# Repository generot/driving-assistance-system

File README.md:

# Driving Assistance System
Дипломна работа 2023 г. на Мартин Наков - Система за напътстване на шофьор на базата на стерео компютърно зрение.

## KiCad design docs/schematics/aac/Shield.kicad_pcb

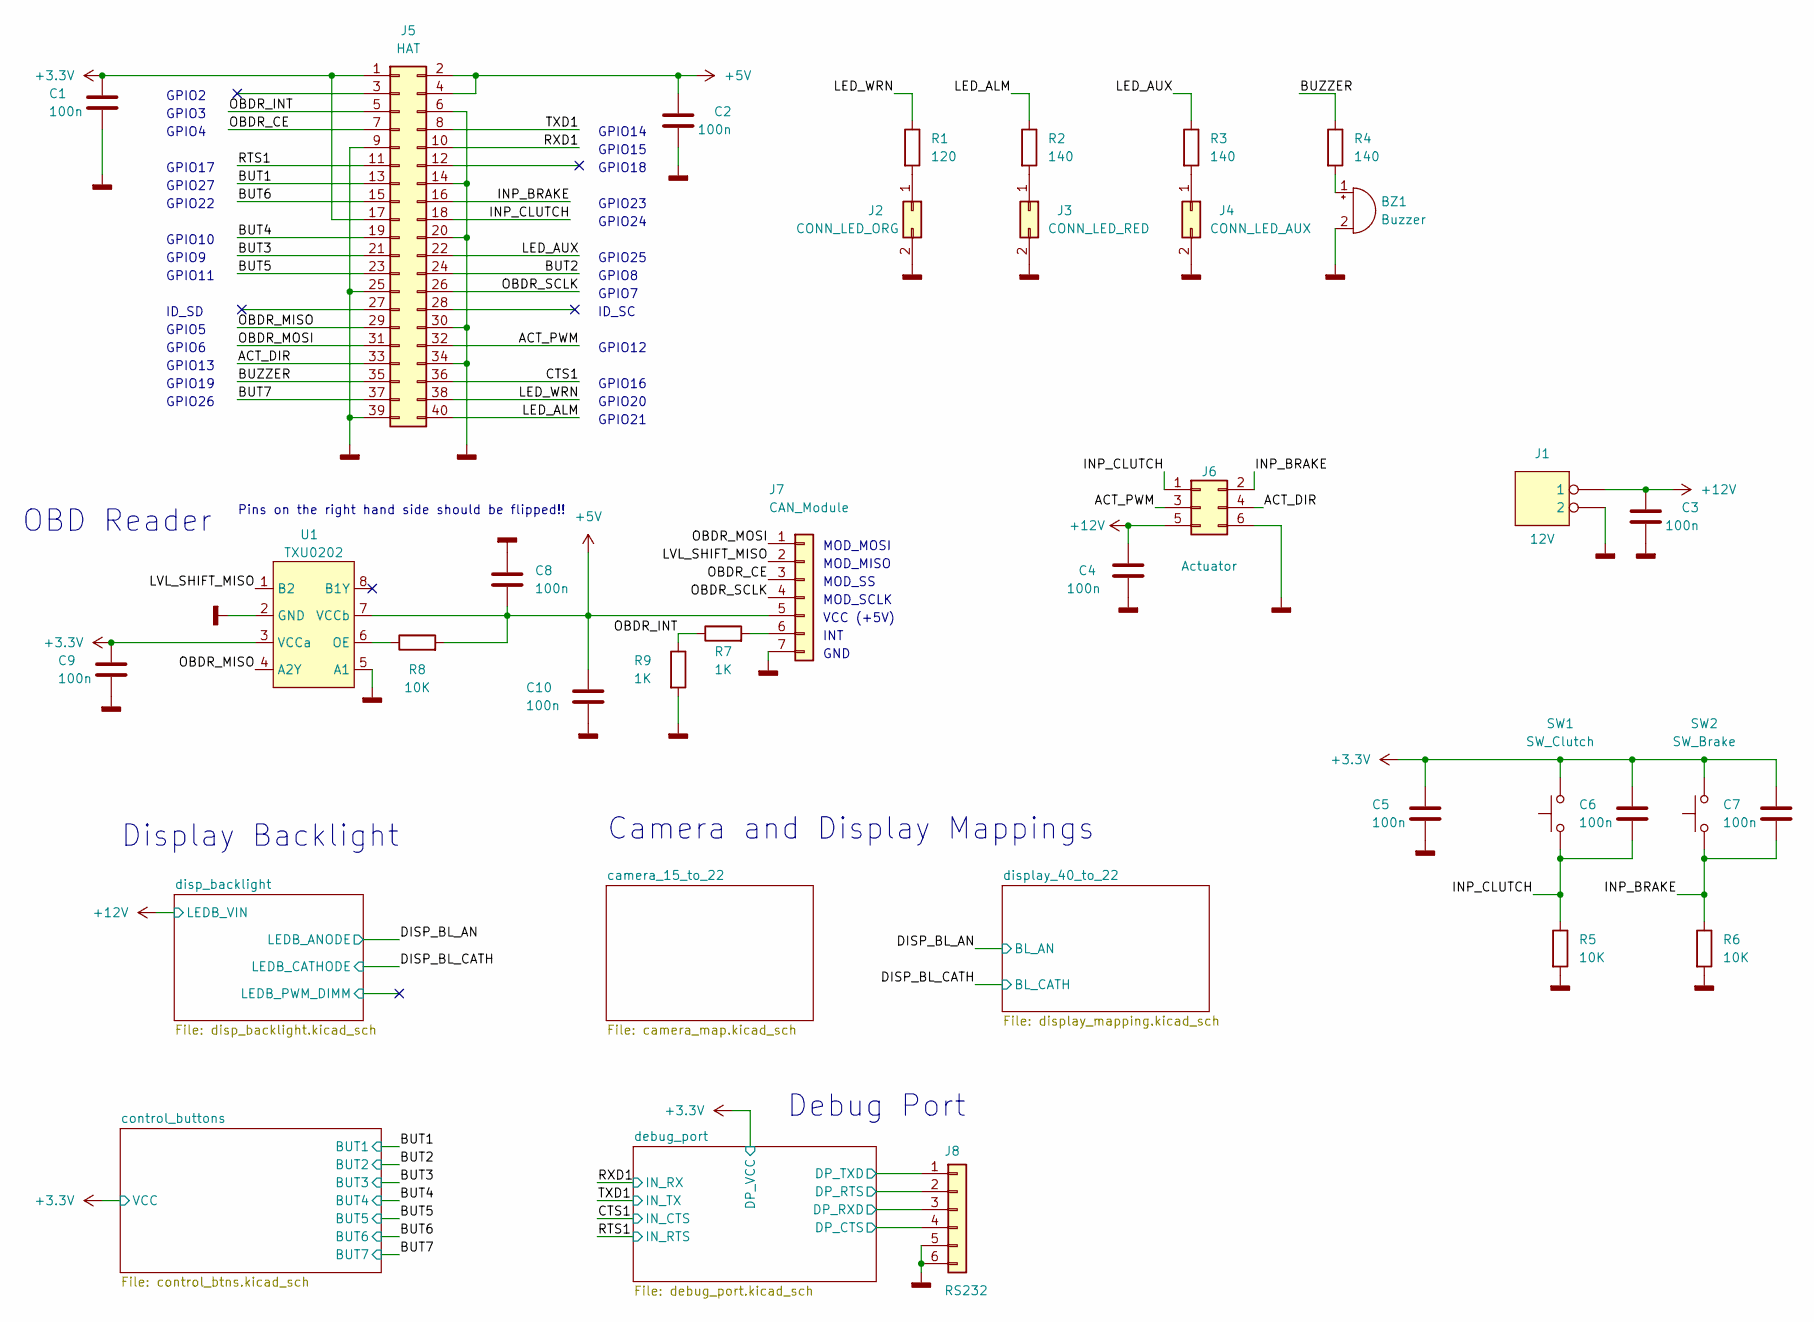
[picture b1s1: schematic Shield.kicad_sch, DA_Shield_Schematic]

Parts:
BZ1: Buzzer; Buzzer_12x9.5RM7.6
C1, C2, C3, C4, C5, C6, C7, C8, C9, C10: 100n; C_0805_2012Metric
J1: 12V; PinHeader_1x02_P2.54mm_Horizontal
J2: CONN_LED_ORG; PinHeader_2x01_P2.54mm_Horizontal
J3: CONN_LED_RED; PinHeader_2x01_P2.54mm_Horizontal
J4: CONN_LED_AUX; PinHeader_2x01_P2.54mm_Horizontal
J5: HAT; PinHeader_2x20_P2.54mm_Vertical
J6: Actuator; PinHeader_2x03_P2.54mm_Vertical
J7: CAN_Module; PinHeader_1x07_P2.54mm_Vertical
J8: RS232; PinHeader_1x06_P2.54mm_Horizontal
R1: 120; R_0805_2012Metric
R2, R3, R4: 140; R_0805_2012Metric
R5, R6, R8: 10K; R_0805_2012Metric
R7, R9: 1K; R_0805_2012Metric
SW1: SW_Clutch; PinHeader_2x01_P2.54mm_Horizontal
SW2: SW_Brake; PinHeader_2x01_P2.54mm_Horizontal
U1: TXU0202; VSSOP-8_2.4x2.1mm_P0.5mm

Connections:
+3.3V: C1.1, C5.1, C6.1, C7.1, C9.1, J5.1, J5.17, SW1.2, SW2.2, U1.3 (VCCa); also elsewhere on the board
+5V: C2.1, C8.1, C10.2, J5.2, J5.4, J7.5, R8.2, U1.7 (VCCb)
+12V: C3.1, C4.1, J1.1, J6.5; also elsewhere on the board
/ACT_DIR: J5.33, J6.4
/ACT_PWM: J5.32, J6.3
/BUT1: J5.13; also elsewhere on the board
/BUT2: J5.24; also elsewhere on the board
/BUT3: J5.21; also elsewhere on the board
/BUT4: J5.19; also elsewhere on the board
/BUT5: J5.23; also elsewhere on the board
/BUT6: J5.15; also elsewhere on the board
/BUT7: J5.37; also elsewhere on the board
/BUZZER: J5.35, R4.1
/CTS1: J5.36; also elsewhere on the board
/INP_BRAKE: C7.2, J5.16, J6.2, R6.1, SW2.1
/INP_CLUTCH: C6.2, J5.18, J6.1, R5.1, SW1.1
/LED_ALM: J5.40, R2.1
/LED_AUX: J5.22, R3.1
/LED_WRN: J5.38, R1.1
/LVL_SHIFT_MISO: J7.2, U1.1 (B2)
/OBDR_CE: J5.7, J7.3
/OBDR_INT: J5.5, R7.1, R9.1
/OBDR_MISO: J5.29, U1.4 (A2Y)
/OBDR_MOSI: J5.31, J7.1
/OBDR_SCLK: J5.26, J7.4
/RTS1: J5.11; also elsewhere on the board
/RXD1: J5.10; also elsewhere on the board
/TXD1: J5.8; also elsewhere on the board
/debug_port/DP_CTS: J8.4; also elsewhere on the board
/debug_port/DP_RTS: J8.2; also elsewhere on the board
/debug_port/DP_RXD: J8.3; also elsewhere on the board
/debug_port/DP_TXD: J8.1; also elsewhere on the board
GNDD: BZ1.2 (+), C1.2, C2.2, C3.2, C4.2, C5.2, C8.2, C9.2, C10.1, J1.2, J2.2, J3.2, J4.2, J5.6, J5.9, J5.14, J5.20, J5.25, J5.30, J5.34, J5.39, J6.6, J7.7, J8.5, J8.6, R5.2, R6.2, R9.2, U1.2 (GND), U1.5 (A1); also elsewhere on the board
unnamed: BZ1.1 (-), R4.2
unnamed: J2.1, R1.2
unnamed: J3.1, R2.2
unnamed: J4.1, R3.2
unnamed: J7.6, R7.2
unnamed: R8.1, U1.6 (OE)

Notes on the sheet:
INT
OBD Reader
GPIO15
GPIO2
GPIO5
GPIO25
GPIO18
GPIO4
GND
GPIO11
MOD_MISO
GPIO8
GPIO10
GPIO16
GPIO7
GPIO23
GPIO22
GPIO17
MOD_SS
MOD_MOSI
GPIO14
GPIO6
GPIO19
GPIO24
Pins on the right hand side should be flipped!!
GPIO9
GPIO3
MOD_SCLK
GPIO20
GPIO21
GPIO12
GPIO26
ID_SC
GPIO27
Display Backlight
GPIO13
ID_SD
Debug Port
VCC (+5V)
Camera and Display Mappings

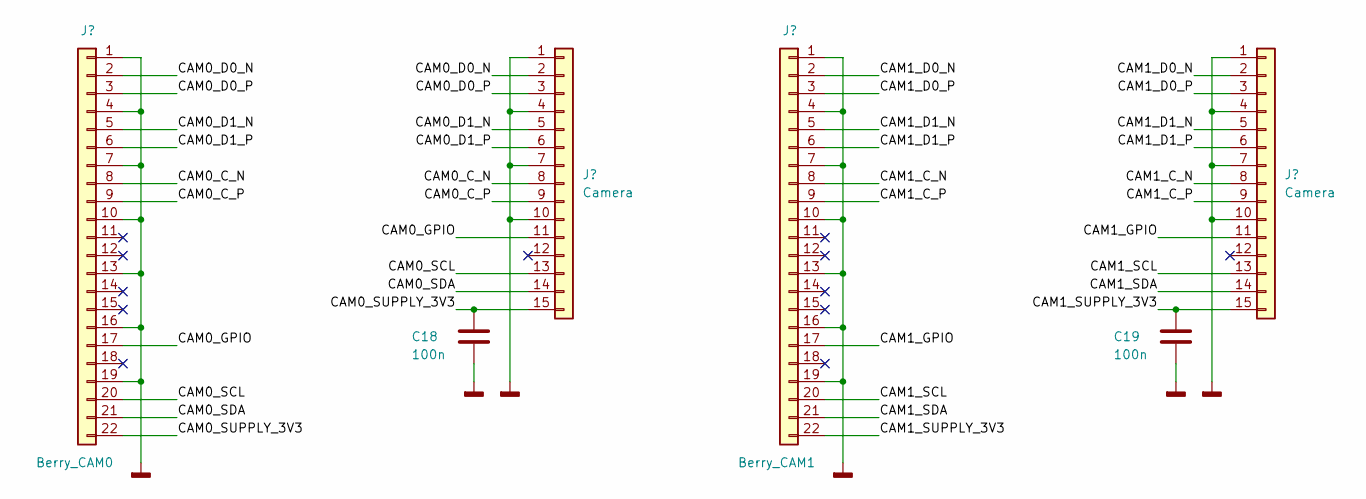
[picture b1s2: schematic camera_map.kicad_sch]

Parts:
C18, C19: 100n; C_0805_2012Metric
J9, J10: Camera; TE_1-84952-5_1x15-1MP_P1.0mm_Horizontal
J11: Berry_CAM0; Hirose_FH12-22S-0.5SH_1x22-1MP_P0.50mm_Horizontal
J12: Berry_CAM1; Hirose_FH12-22S-0.5SH_1x22-1MP_P0.50mm_Horizontal

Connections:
/camera_15_to_22/CAM0_C_N: J9.8, J11.8
/camera_15_to_22/CAM0_C_P: J9.9, J11.9
/camera_15_to_22/CAM0_D0_N: J9.2, J11.2
/camera_15_to_22/CAM0_D0_P: J9.3, J11.3
/camera_15_to_22/CAM0_D1_N: J9.5, J11.5
/camera_15_to_22/CAM0_D1_P: J9.6, J11.6
/camera_15_to_22/CAM0_GPIO: J9.11, J11.17
/camera_15_to_22/CAM0_SCL: J9.13, J11.20
/camera_15_to_22/CAM0_SDA: J9.14, J11.21
/camera_15_to_22/CAM0_SUPPLY_3V3: C18.1, J9.15, J11.22
/camera_15_to_22/CAM1_C_N: J10.8, J12.8
/camera_15_to_22/CAM1_C_P: J10.9, J12.9
/camera_15_to_22/CAM1_D0_N: J10.2, J12.2
/camera_15_to_22/CAM1_D0_P: J10.3, J12.3
/camera_15_to_22/CAM1_D1_N: J10.5, J12.5
/camera_15_to_22/CAM1_D1_P: J10.6, J12.6
/camera_15_to_22/CAM1_GPIO: J10.11, J12.17
/camera_15_to_22/CAM1_SCL: J10.13, J12.20
/camera_15_to_22/CAM1_SDA: J10.14, J12.21
/camera_15_to_22/CAM1_SUPPLY_3V3: C19.1, J10.15, J12.22
GNDD: C18.2, C19.2, J9.1, J9.4, J9.7, J9.10, J9.MP, J10.1, J10.4, J10.7, J10.10, J10.MP, J11.1, J11.4, J11.7, J11.10, J11.13, J11.16, J11.19, J11.MP, J12.1, J12.4, J12.7, J12.10, J12.13, J12.16, J12.19, J12.MP; also elsewhere on the board

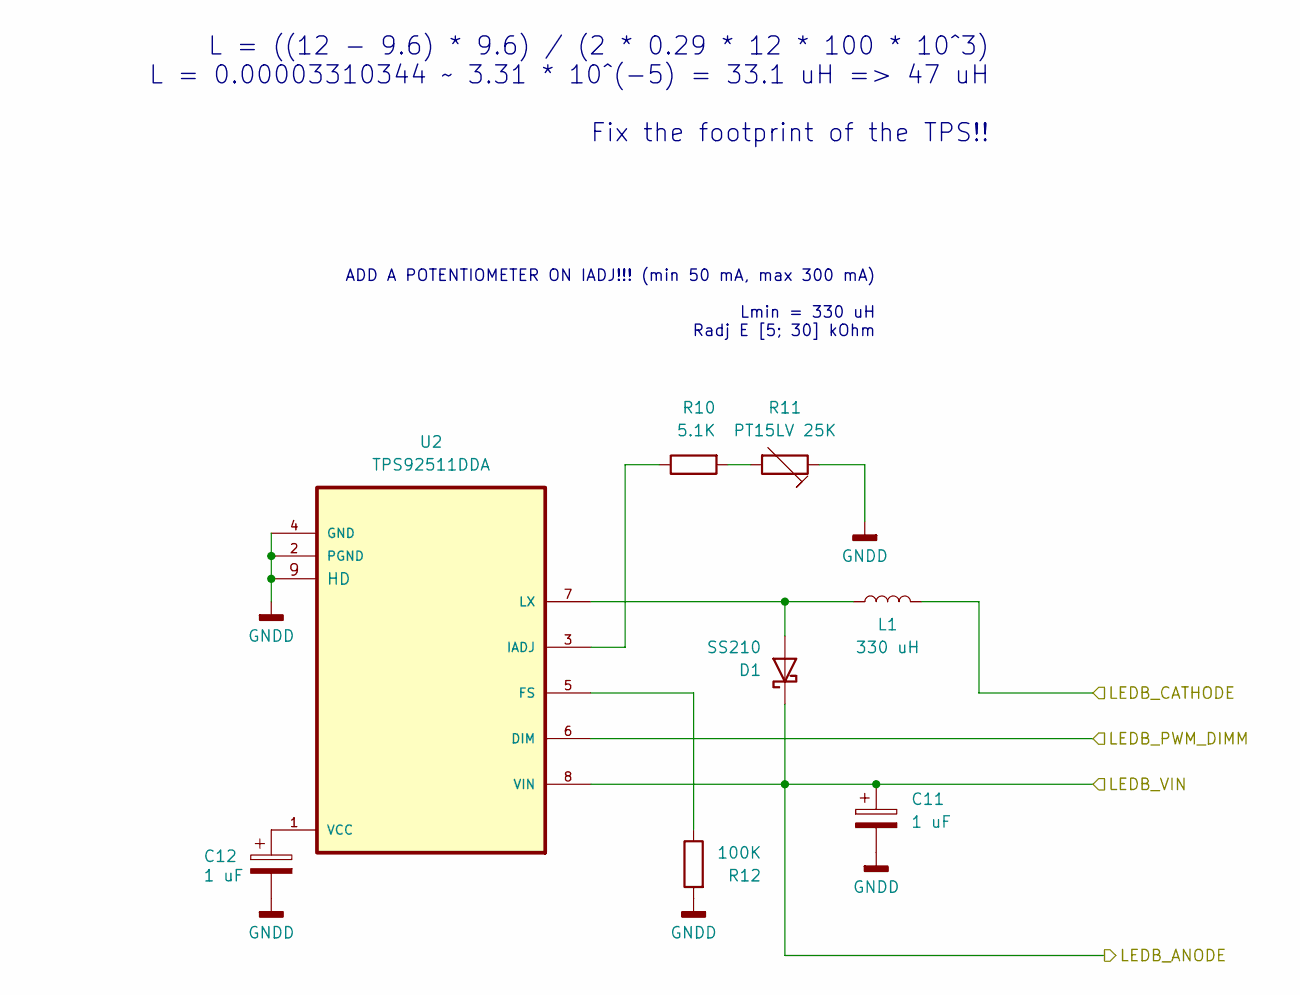
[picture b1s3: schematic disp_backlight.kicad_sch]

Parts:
C11, C12: 1 uF; C_0805_2012Metric
D1: SS210; D_SMB
L1: 330 uH; L_SigTra_SC3316F
R10: 5.1K; R_0805_2012Metric
R11: PT15LV 25K; Potentiometer_ACP_CA14V-15_Vertical
R12: 100K; R_0805_2012Metric
U2: TPS92511DDA; SOIC-8-1EP_3.9x4.9mm_P1.27mm_EP2.29x3mm_ThermalVias

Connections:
+12V: C11.1, D1.1 (K), U2.8 (VIN); also elsewhere on the board
/DISP_BL_CATH: L1.2; also elsewhere on the board
/disp_backlight/LEDB_PWM_DIMM: U2.6 (DIM)
GNDD: C11.2, C12.2, R11.1, R12.2, U2.2 (PGND), U2.4 (GND), U2.9 (HD); also elsewhere on the board
unnamed: D1.2 (A), L1.1, U2.7 (LX)
unnamed: R10.2, R11.2
unnamed: R12.1, U2.5 (FS)
unnamed: R10.1, U2.3 (IADJ)
unnamed: C12.1, U2.1 (VCC)

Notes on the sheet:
ADD A POTENTIOMETER ON IADJ!!! (min 50 mA, max 300 mA) Lmin = 330 uH Radj E [5; 30] kOhm
L = ((12 - 9.6) * 9.6) / (2 * 0.29 * 12 * 100 * 10^3) L = 0.00003310344 ~ 3.31 * 10^(-5) = 33.1 uH => 47 uH Fix the footprint of the TPS!!

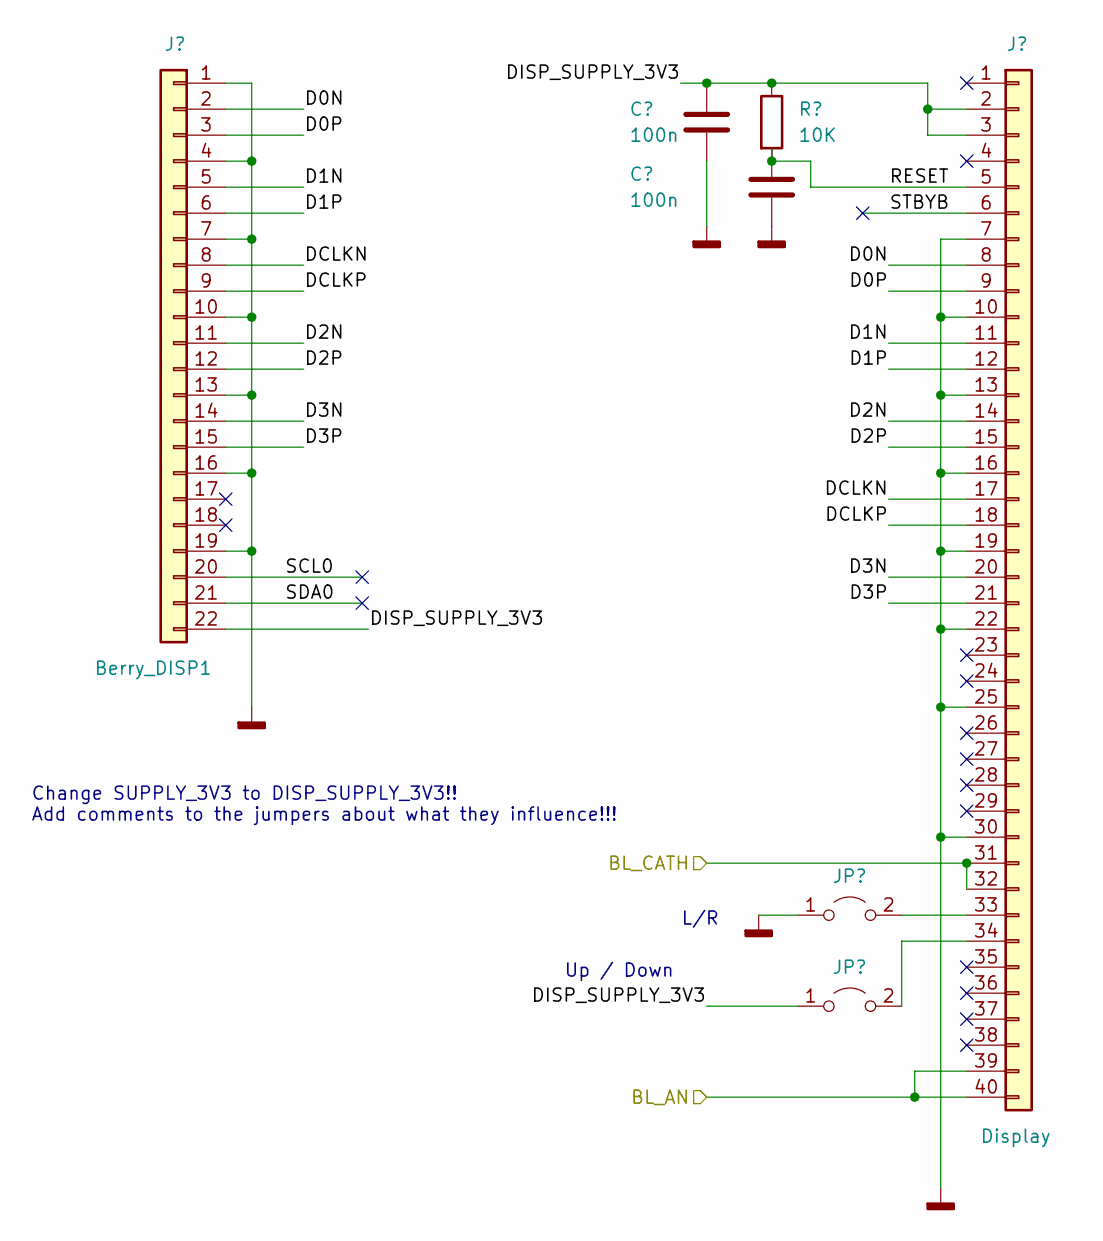
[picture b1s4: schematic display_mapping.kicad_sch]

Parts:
C28, C29: 100n; C_0805_2012Metric
J20: Berry_DISP1; Hirose_FH12-22S-0.5SH_1x22-1MP_P0.50mm_Horizontal
J21: Display; Hirose_FH12-40S-0.5SH_1x40-1MP_P0.50mm_Horizontal
JP1, JP2: Jumper_2_Open; SolderJumper-2_P1.3mm_Open_RoundedPad1.0x1.5mm
R20: 10K; R_0805_2012Metric

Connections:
+12V: J21.39, J21.40; also elsewhere on the board
/DISP_BL_CATH: J21.31, J21.32; also elsewhere on the board
/display_40_to_22/D0N: J20.2, J21.8
/display_40_to_22/D0P: J20.3, J21.9
/display_40_to_22/D1N: J20.5, J21.11
/display_40_to_22/D1P: J20.6, J21.12
/display_40_to_22/D2N: J20.11, J21.14
/display_40_to_22/D2P: J20.12, J21.15
/display_40_to_22/D3N: J20.14, J21.20
/display_40_to_22/D3P: J20.15, J21.21
/display_40_to_22/DCLKN: J20.8, J21.17
/display_40_to_22/DCLKP: J20.9, J21.18
/display_40_to_22/DISP_SUPPLY_3V3: C28.1, J20.22, J21.2, J21.3, JP2.1 (A), R20.1
/display_40_to_22/RESET: C29.1, J21.5, R20.2
/display_40_to_22/SCL0: J20.20
/display_40_to_22/SDA0: J20.21
/display_40_to_22/STBYB: J21.6
GNDD: C28.2, C29.2, J20.1, J20.4, J20.7, J20.10, J20.13, J20.16, J20.19, J20.MP, J21.7, J21.10, J21.13, J21.16, J21.19, J21.22, J21.25, J21.30, J21.MP, JP1.1 (A); also elsewhere on the board
unnamed: J21.33, JP1.2 (B)
unnamed: J21.34, JP2.2 (B)

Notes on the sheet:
L/R
Change SUPPLY_3V3 to DISP_SUPPLY_3V3!! Add comments to the jumpers about what they influence!!!
Up / Down

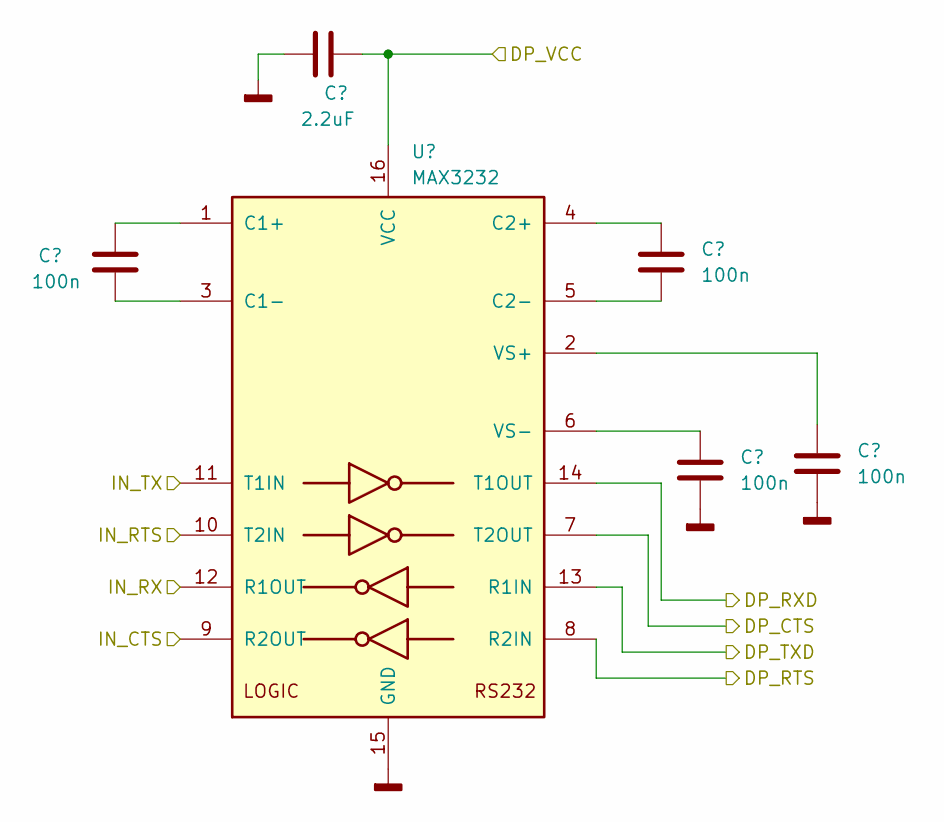
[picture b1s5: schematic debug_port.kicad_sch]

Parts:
C13: 2.2uF; C_0805_2012Metric
C14, C15, C16, C17: 100n; C_0805_2012Metric
U3: MAX3232; SO-16_5.3x10.2mm_P1.27mm

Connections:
+3.3V: C13.2, U3.16 (VCC); also elsewhere on the board
/CTS1: U3.9 (R2OUT); also elsewhere on the board
/RTS1: U3.10 (T2IN); also elsewhere on the board
/RXD1: U3.12 (R1OUT); also elsewhere on the board
/TXD1: U3.11 (T1IN); also elsewhere on the board
/debug_port/DP_CTS: U3.7 (T2OUT); also elsewhere on the board
/debug_port/DP_RTS: U3.8 (R2IN); also elsewhere on the board
/debug_port/DP_RXD: U3.14 (T1OUT); also elsewhere on the board
/debug_port/DP_TXD: U3.13 (R1IN); also elsewhere on the board
GNDD: C13.1, C16.2, C17.2, U3.15 (GND); also elsewhere on the board
unnamed: C14.1, U3.1 (C1+)
unnamed: C14.2, U3.3 (C1-)
unnamed: C15.1, U3.4 (C2+)
unnamed: C15.2, U3.5 (C2-)
unnamed: C16.1, U3.2 (VS+)
unnamed: C17.1, U3.6 (VS-)

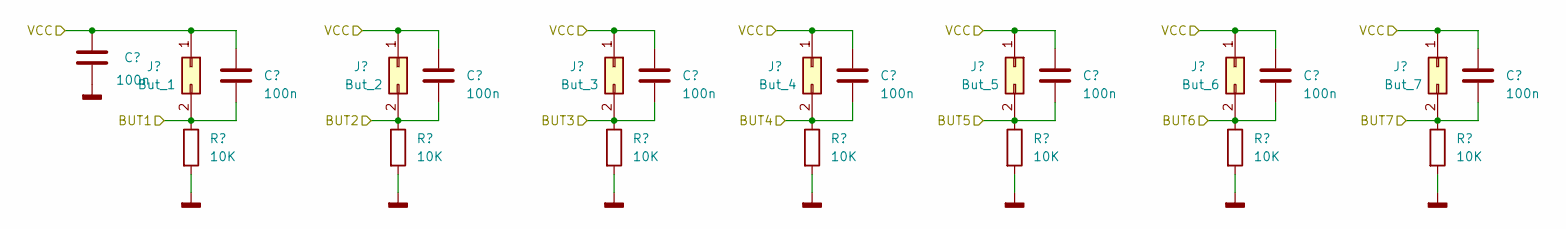
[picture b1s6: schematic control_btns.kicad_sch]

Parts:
C20, C21, C22, C23, C24, C25, C26, C27: 100n; C_0805_2012Metric
J13: But_1; PinHeader_2x01_P2.54mm_Horizontal
J14: But_2; PinHeader_2x01_P2.54mm_Horizontal
J15: But_3; PinHeader_2x01_P2.54mm_Horizontal
J16: But_4; PinHeader_2x01_P2.54mm_Horizontal
J17: But_5; PinHeader_2x01_P2.54mm_Horizontal
J18: But_6; PinHeader_2x01_P2.54mm_Horizontal
J19: But_7; PinHeader_2x01_P2.54mm_Horizontal
R13, R14, R15, R16, R17, R18, R19: 10K; R_0805_2012Metric

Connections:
+3.3V: C20.1, C21.1, C22.1, C23.1, C24.1, C25.1, C26.1, C27.1, J13.1, J14.1, J15.1, J16.1, J17.1, J18.1, J19.1; also elsewhere on the board
/BUT1: C21.2, J13.2, R13.1; also elsewhere on the board
/BUT2: C22.2, J14.2, R14.1; also elsewhere on the board
/BUT3: C23.2, J15.2, R15.1; also elsewhere on the board
/BUT4: C24.2, J16.2, R16.1; also elsewhere on the board
/BUT5: C25.2, J17.2, R17.1; also elsewhere on the board
/BUT6: C26.2, J18.2, R18.1; also elsewhere on the board
/BUT7: C27.2, J19.2, R19.1; also elsewhere on the board
GNDD: C20.2, R13.2, R14.2, R15.2, R16.2, R17.2, R18.2, R19.2; also elsewhere on the board

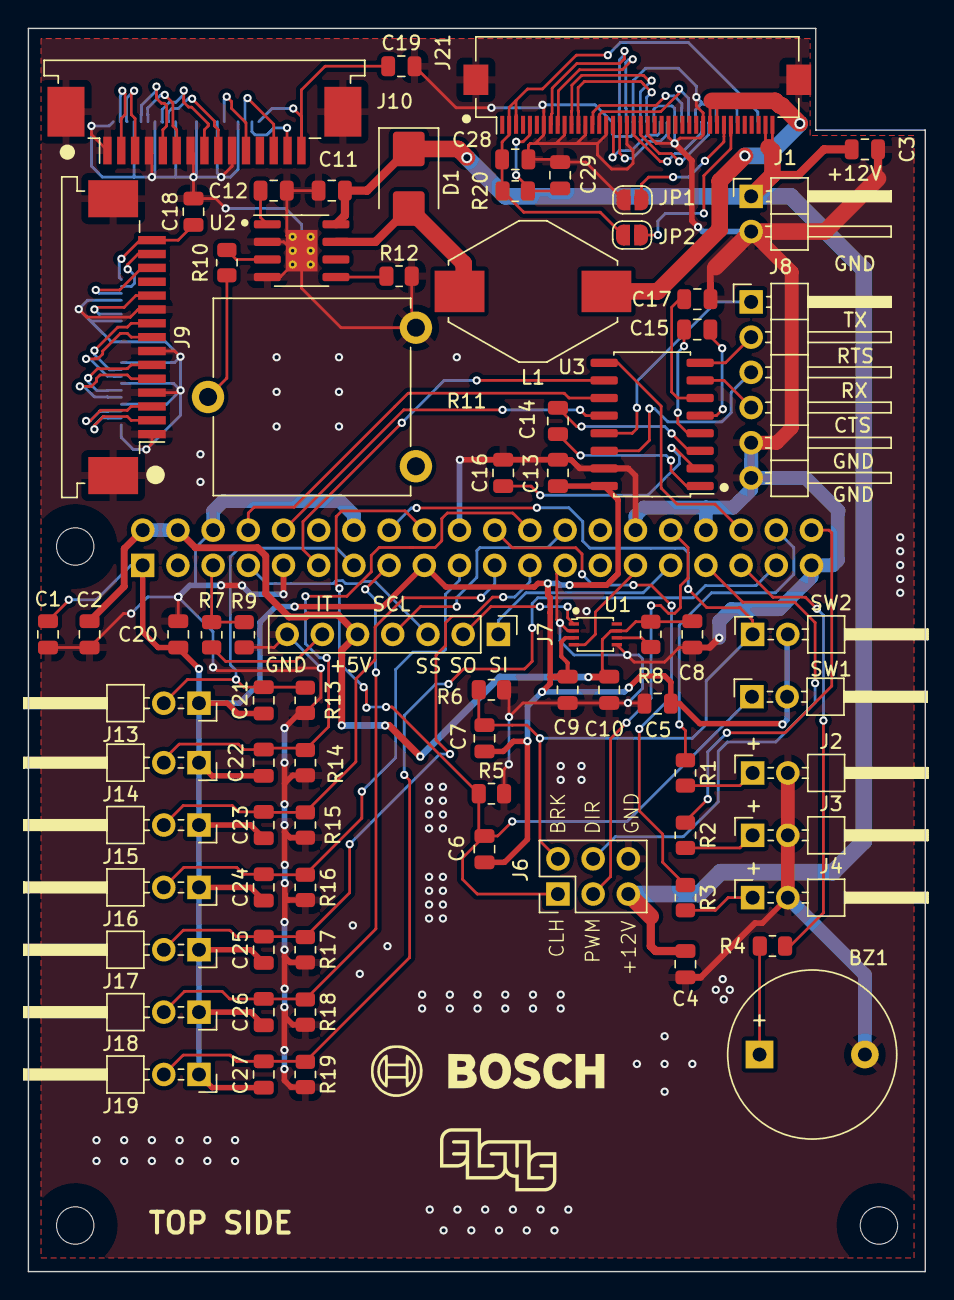
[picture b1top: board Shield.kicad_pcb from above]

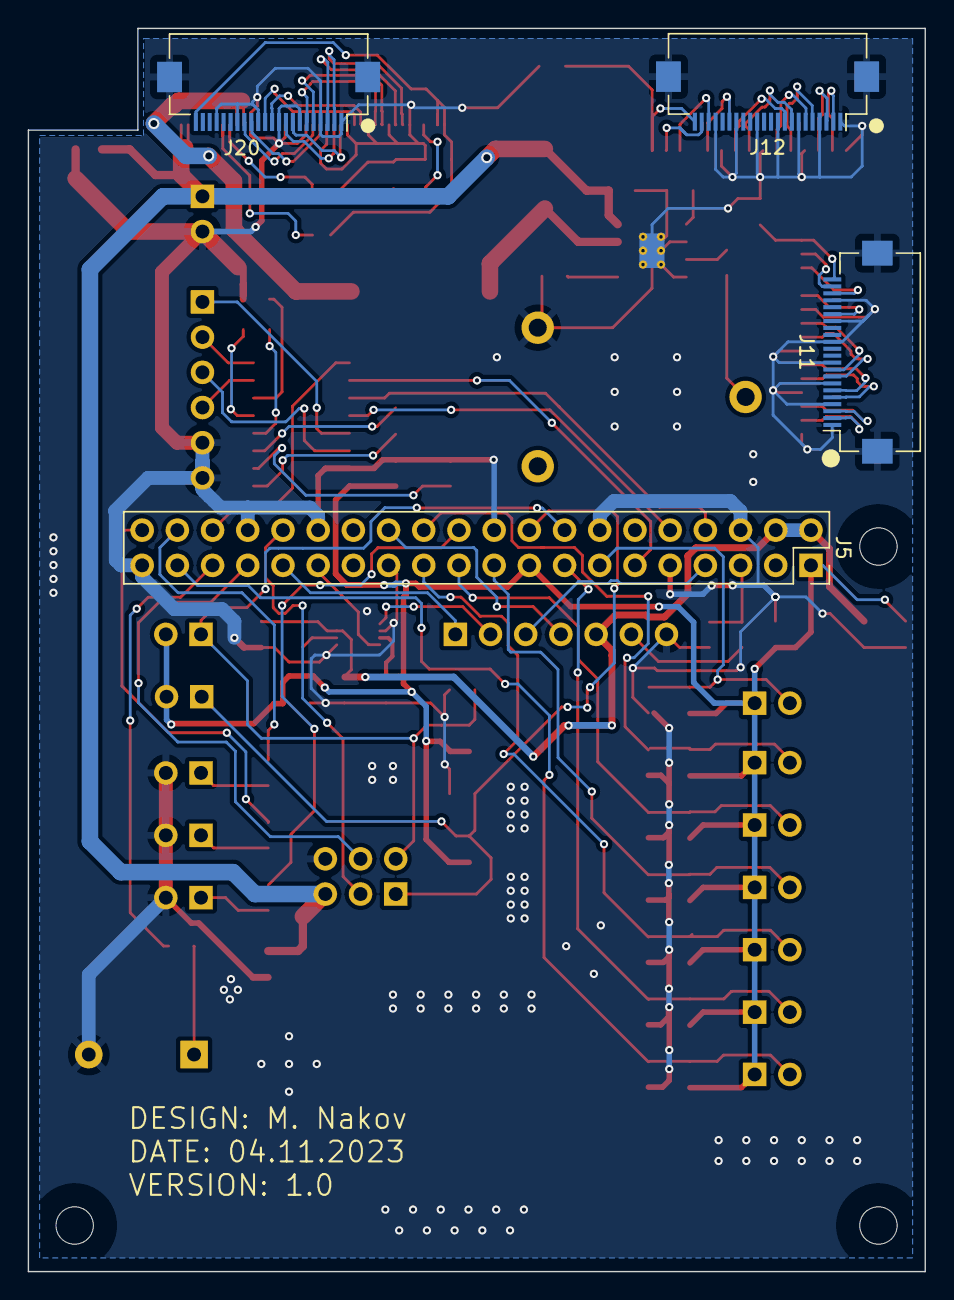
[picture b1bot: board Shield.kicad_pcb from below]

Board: 2 copper layers, 64.7 x 89.7 mm, 83 parts (4 on the bottom side), 85 nets.

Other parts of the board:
H2, H3, H4: MountingHole; MountingHole_2.7mm_M2.5

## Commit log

2023-09-07 Pushing docs to repo.
2023-09-07 Updated components list
2023-09-07 Testing push from Raspbian VM
2023-09-08 Simplistic car detection added
2023-09-10 Strategy update, details in components.xlsx and daily_updates.txt
2023-09-11 Made a basic traffic sign detection, based on Hough Circle transform
2023-09-12 Implemented acceptable SL recognition with color filtering and Hough transform
2023-09-12 Status update
2023-09-14 Generating disparity maps from stereo-pair images
2023-09-14 Adding samples
2023-09-15 Made better disparity filtering and implemented basic depth estimation with template matching.
2023-09-15 Implemented depth estimation in a made up scenario.
2023-09-21 Minor update, written in docs
2023-09-24 Merged car detection with TSR
2023-09-25 Made basic kNN model for TSR
2023-09-25 smth
2023-09-26 Implemented some what working SL recognition
2023-09-27 Made a basic vehicle transmission simulation for the PID controller PoC.
2023-09-28 Wrote an example PID controller
2023-09-28 Bug fix: TSR no longer captures a frame when a matrix with 0 rows (i.e. a line) is provided
2023-10-03 Implemented bare-bone digit recognition.
2023-10-03 Refactored detect.py
2023-10-03 Abstracted away some training functionality.
2023-10-03 Added daily update
2023-10-04 Pushing project architecture chart.
2023-10-13 Implementing camera calibration; augmented car detection algorithm for night driving;
2023-10-24 Pushing all schematics to repo
2023-11-07 Pushing final schematic and PCB.
2023-11-24 Updating repo with most recent changes
2024-01-10 Implemented frame pulling from stereo camera set
2024-01-10 Implemented multiprocessing, but unfortunately it doesn't work correctly
2024-01-14 Implemented device tree overlay for the display.
2024-01-16 Made some patches to the display DTO, about to see if it works.
2024-01-23 Added DTO for the custom driver
2024-01-30 Device Tree Overlays for the CAN Bus implemented
2024-01-30 Caching credentials
2024-02-03 Car detection and camera calibration setup
2024-02-04 Implemented working triangulation
2024-02-04 Distance detection sort of works now!
2024-02-05 Implemented all required features (finally)
2024-02-06 Increased camera capture area to the maximum provided by the sensor and increased speed of Haar cascade
2024-03-27 Commiting KNN dataset and better TSR
2024-04-25 Providing full TSR implementation.
